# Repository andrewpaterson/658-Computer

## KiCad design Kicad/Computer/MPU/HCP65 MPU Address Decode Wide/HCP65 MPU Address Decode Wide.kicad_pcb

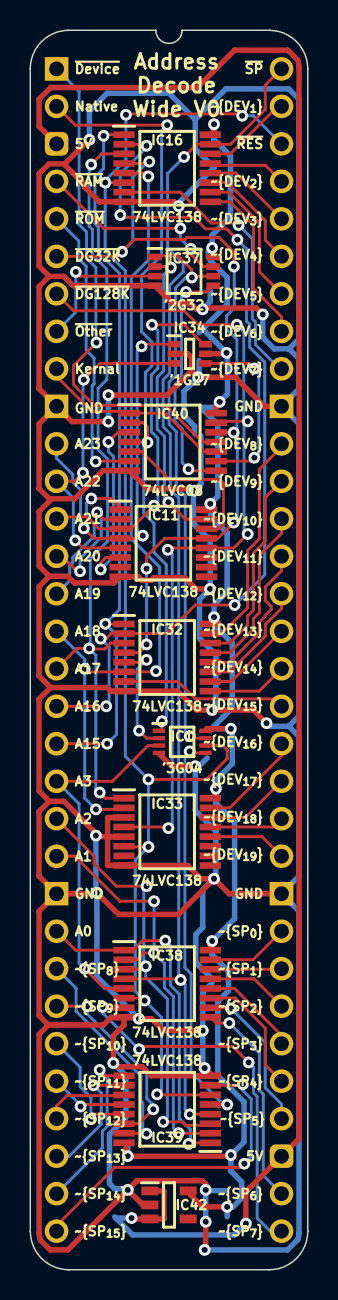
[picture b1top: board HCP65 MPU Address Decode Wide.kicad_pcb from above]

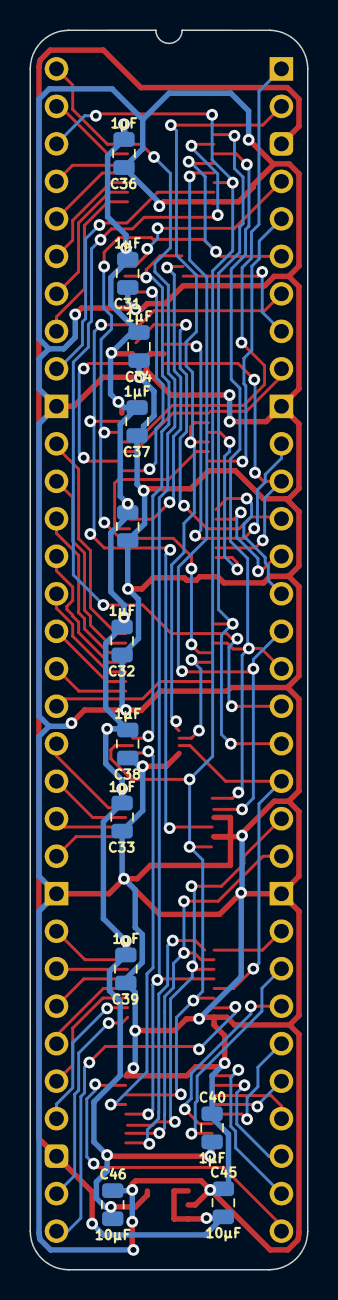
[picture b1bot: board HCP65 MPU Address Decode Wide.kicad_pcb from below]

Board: 2 copper layers, 18.8 x 84.0 mm, 26 parts (14 on the bottom side), 69 nets.

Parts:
C31, C32, C33, C34, C35, C36, C37, C38, C39, C40: 1μF; C_0805
C45, C46: 10μF; C_0805
IC1: SN74LVC3G04DCUR; SOP50P310X90-8N
IC11, IC16, IC32, IC33, IC38, IC39: 74LVC138APW-Q100J; SOP65P640X110-16N
IC34: 74LVC1G27GW,125; SOP65P210X110-6N
IC37: 74LVC2G32DP,125; SOP65P400X110-8N
IC40: 74LVC08APW,112; SOP65P640X110-14N
IC42: AP7365-33WG-7; SOT95P285X130-5N
J1, J3: Pin_Header_01x32; PinHeader_1x32_P2.54mm_Vertical
J2: Conn_02x32_Counter_Clockwise; DIP-64_Board_W15.24mm

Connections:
5V: C45.1, IC42.1 (6VIn), IC42.3 (EN), J2.3, J2.35
/3.3V: C31.1, C32.1, C33.1, C34.1, C35.1, C36.1, C37.1, C38.1, C39.1, C40.1, C46.1, IC1.8 (3V), IC11.16 (3V), IC16.16 (3V), IC32.16 (3V), IC33.16 (3V), IC34.5 (3V), IC37.8 (VCC), IC38.16 (3V), IC39.16 (3V), IC40.14 (3V), IC42.5 (3.3VOut)
/Kernal Mode·Native Latch: IC11.6 (E3), IC40.3 (1Y)
/Reset: IC1.2 (3Y), IC32.5 (~E2)
/~A3: IC1.5 (2Y), IC39.5 (~E2)
/~A21+A22+A23: IC34.4 (Y), IC40.9 (3A)
/~Native Latch: IC1.7 (1Y), IC37.1 (1A), IC37.6 (2B)
/~RAM: IC11.15 (~Y0), IC37.2 (1B)
/~ROM: IC11.14 (~Y1), IC40.5 (2B)
A0: IC38.1 (A0), IC39.1 (A0), J2.24
A1: IC38.2 (A1), IC39.2 (A1), J2.22
A2: IC38.3 (A2), IC39.3 (A2), J2.21
A3: IC1.3 (2A), IC38.5 (~E2), J2.20
A15: IC16.1 (A0), IC32.1 (A0), J2.19
A16: IC16.2 (A1), IC32.2 (A1), J2.18
A17: IC16.3 (A2), IC32.3 (A2), IC33.1 (A0), J2.17
A18: IC16.5 (~E2), IC32.6 (E3), IC33.2 (A1), J2.16
A19: IC11.1 (A0), J2.15
A20: IC11.2 (A1), J2.14
A21: IC11.3 (A2), IC34.6 (C), J2.13
A22: IC11.5 (~E2), IC34.3 (B), J2.12
A23: IC11.4 (~E1), IC34.1 (A), J2.11
GND: C31.2, C32.2, C33.2, C34.2, C35.2, C36.2, C37.2, C38.2, C39.2, C40.2, C45.2, C46.2, IC1.4 (GND), IC11.8 (GND), IC16.8 (GND), IC32.8 (GND), IC33.3 (A2), IC33.5 (~E2), IC33.8 (GND), IC34.2 (GND), IC37.4 (GND), IC38.8 (GND), IC39.8 (GND), IC40.7 (GND), IC42.2 (GND), J2.10, J2.23, J2.42, J2.55
Kernal Mode: IC40.1 (1A), IC40.10 (3B), J2.9
Native Latch: IC1.1 (1A), IC40.2 (1B), IC40.4 (2A), J2.2
unnamed: IC37.5 (2A), IC40.8 (3Y)
~Device Group 32K: IC11.13 (~Y2), IC16.4 (~E1), IC32.4 (~E1), IC40.12 (4A), J2.6
~Device Group 128K: IC11.12 (~Y3), IC33.4 (~E1), IC40.13 (4B), J2.7
~Device _{CS1}: IC16.14 (~Y1), J2.63
~Device _{CS2}: IC16.13 (~Y2), J2.61
~Device _{CS3}: IC16.12 (~Y3), J2.60
~Device _{CS4}: IC16.11 (~Y4), J2.59
~Device _{CS5}: IC16.10 (~Y5), J2.58
~Device _{CS6}: IC16.9 (~Y6), J2.57
~Device _{CS7}: IC16.7 (~Y7), J2.56
~Device _{CS8}: IC32.15 (~Y0), J2.54
~Device _{CS9}: IC32.14 (~Y1), J2.53
~Device _{CS10}: IC32.13 (~Y2), J2.52
~Device _{CS11}: IC32.12 (~Y3), J2.51
~Device _{CS12}: IC32.11 (~Y4), J2.50
~Device _{CS13}: IC32.10 (~Y5), J2.49
~Device _{CS14}: IC32.9 (~Y6), J2.48
~Device _{CS15}: IC32.7 (~Y7), J2.47
~Device _{CS16}: IC33.15 (~Y0), J2.46
~Device _{CS17}: IC33.14 (~Y1), J2.45
~Device _{CS18}: IC33.13 (~Y2), J2.44
~Device _{CS19}: IC33.12 (~Y3), J2.43
~Device: IC40.11 (4Y), J2.1
~OTHER: IC37.3 (2Y), J2.8
~RAM_{CS}: IC37.7 (1Y), J2.4
~ROM_{CS}: IC40.6 (2Y), J2.5
~Reset: IC1.6 (3A), IC16.6 (E3), IC33.6 (E3), IC38.6 (E3), IC39.6 (E3), J2.62
~SPECIAL: IC16.15 (~Y0), IC38.4 (~E1), IC39.4 (~E1), J2.64
~Special _{CS0}: IC38.15 (~Y0), J2.41
~Special _{CS1}: IC38.14 (~Y1), J2.40
~Special _{CS2}: IC38.13 (~Y2), J2.39
~Special _{CS3}: IC38.12 (~Y3), J2.38
~Special _{CS4}: IC38.11 (~Y4), J2.37
~Special _{CS5}: IC38.10 (~Y5), J2.36
~Special _{CS6}: IC38.9 (~Y6), J2.34
~Special _{CS7}: IC38.7 (~Y7), J2.33
~Special _{CS8}: IC39.15 (~Y0), J2.25
~Special _{CS9}: IC39.14 (~Y1), J2.26
~Special _{CS10}: IC39.13 (~Y2), J2.27
~Special _{CS11}: IC39.12 (~Y3), J2.28
~Special _{CS12}: IC39.11 (~Y4), J2.29
~Special _{CS13}: IC39.10 (~Y5), J2.30
~Special _{CS14}: IC39.9 (~Y6), J2.31
~Special _{CS15}: IC39.7 (~Y7), J2.32

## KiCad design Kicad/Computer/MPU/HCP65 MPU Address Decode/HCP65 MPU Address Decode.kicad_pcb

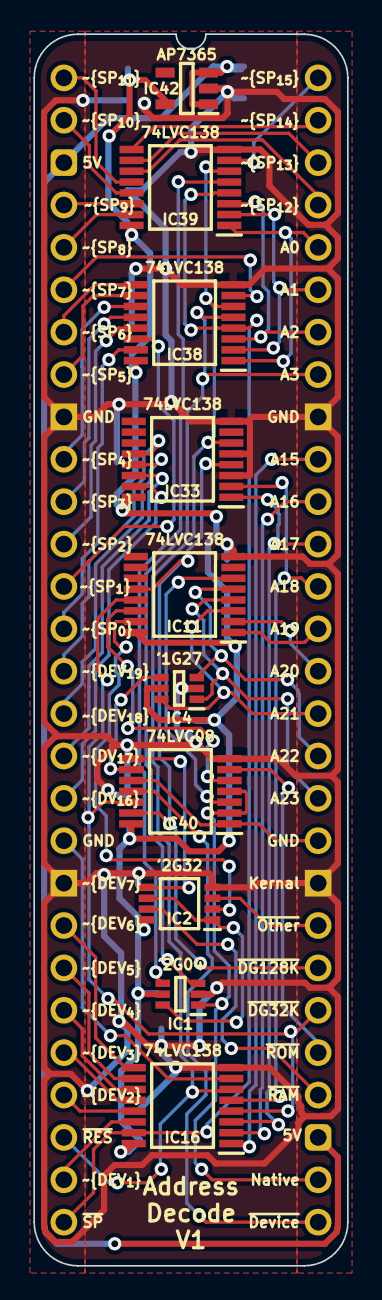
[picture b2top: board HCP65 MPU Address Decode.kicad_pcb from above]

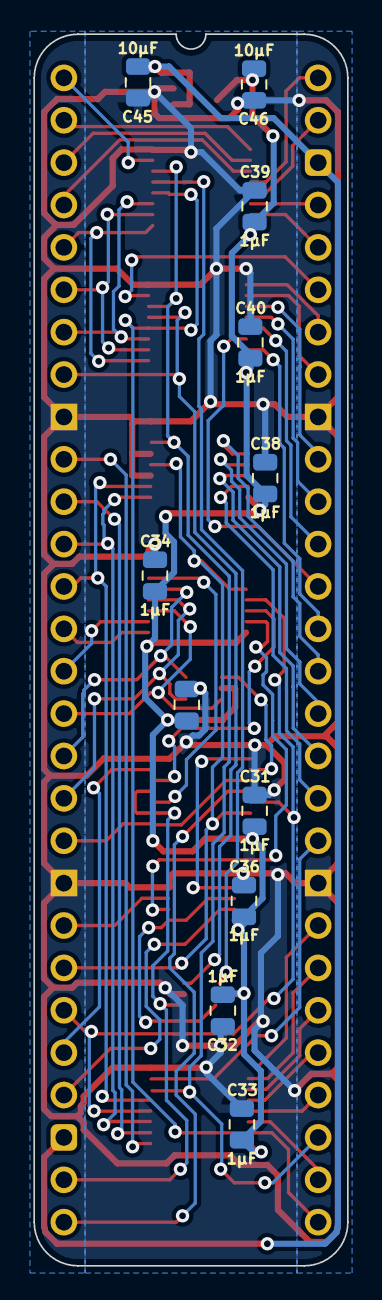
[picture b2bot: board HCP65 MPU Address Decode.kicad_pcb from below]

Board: 2 copper layers, 18.8 x 73.8 mm, 24 parts (13 on the bottom side), 60 nets.

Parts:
C31, C32, C33, C34, C35, C36, C38, C39, C40: 1μF; C_0805
C45, C46: 10μF; C_0805
IC1: 74LVC2G04GW-Q100H; SOP65P210X110-6N
IC2: 74LVC2G32DP,125; SOP65P400X110-8N
IC4: 74LVC1G27GW,125; SOP65P210X110-6N
IC11, IC16, IC33, IC38, IC39: 74LVC138APW-Q100J; SOP65P640X110-16N
IC40: 74LVC08APW,112; SOP65P640X110-14N
IC42: AP7365-33WG-7; SOT95P285X130-5N
J1, J3: Pin_Header_01x28; PinHeader_1x28_P2.54mm_Vertical
J2: Conn_02x28_Counter_Clockwise; DIP-56_Board_W15.24mm

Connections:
5V: C45.1, IC42.1 (6VIn), IC42.3 (EN), J2.3, J2.31
/3.3V: C31.1, C32.1, C33.1, C34.1, C35.1, C36.1, C38.1, C39.1, C40.1, C46.1, IC1.5 (3V), IC2.8 (VCC), IC4.5 (3V), IC11.16 (3V), IC16.16 (3V), IC33.16 (3V), IC38.16 (3V), IC39.16 (3V), IC40.14 (3V), IC42.5 (3.3VOut)
/Kernal Mode·Native Latch: IC11.6 (E3), IC40.3 (1Y)
/~A3: IC1.4 (2Y), IC39.5 (~E2)
/~A21+A22+A23: IC4.4 (Y), IC40.9 (3A)
/~Native Latch: IC1.6 (1Y), IC2.1 (1A), IC2.6 (2B)
/~RAM: IC2.2 (1B), IC11.15 (~Y0)
/~ROM: IC11.14 (~Y1), IC40.5 (2B)
A0: IC38.1 (A0), IC39.1 (A0), J2.52
A1: IC38.2 (A1), IC39.2 (A1), J2.51
A2: IC38.3 (A2), IC39.3 (A2), J2.50
A3: IC1.3 (2A), IC38.5 (~E2), J2.49
A15: IC16.1 (A0), J2.47
A16: IC16.2 (A1), J2.46
A17: IC16.3 (A2), IC33.1 (A0), J2.45
A18: IC16.5 (~E2), IC33.2 (A1), J2.44
A19: IC11.1 (A0), J2.43
A20: IC11.2 (A1), J2.42
A21: IC4.6 (C), IC11.3 (A2), J2.41
A22: IC4.3 (B), IC11.5 (~E2), J2.40
A23: IC4.1 (A), IC11.4 (~E1), J2.39
GND: C31.2, C32.2, C33.2, C34.2, C35.2, C36.2, C38.2, C39.2, C40.2, C45.2, C46.2, IC1.2 (GND), IC2.4 (GND), IC4.2 (GND), IC11.8 (GND), IC16.8 (GND), IC33.3 (A2), IC33.5 (~E2), IC33.8 (GND), IC38.8 (GND), IC39.8 (GND), IC40.7 (GND), IC42.2 (GND), J2.9, J2.20, J2.37, J2.48
Kernal Mode: IC40.1 (1A), IC40.10 (3B), J2.38
Native Latch: IC1.1 (1A), IC40.2 (1B), IC40.4 (2A), J2.30
unnamed: IC2.5 (2A), IC40.8 (3Y)
~Device Group 32K: IC11.13 (~Y2), IC16.4 (~E1), IC40.12 (4A), J2.34
~Device Group 128K: IC11.12 (~Y3), IC33.4 (~E1), IC40.13 (4B), J2.35
~Device _{CS1}: IC16.14 (~Y1), J2.27
~Device _{CS2}: IC16.13 (~Y2), J2.25
~Device _{CS3}: IC16.12 (~Y3), J2.24
~Device _{CS4}: IC16.11 (~Y4), J2.23
~Device _{CS5}: IC16.10 (~Y5), J2.22
~Device _{CS6}: IC16.9 (~Y6), J2.21
~Device _{CS7}: IC16.7 (~Y7), J2.19
~Device _{CS16}: IC33.15 (~Y0), J2.18
~Device _{CS17}: IC33.14 (~Y1), J2.17
~Device _{CS18}: IC33.13 (~Y2), J2.16
~Device _{CS19}: IC33.12 (~Y3), J2.15
~Device: IC40.11 (4Y), J2.29
~OTHER: IC2.3 (2Y), J2.36
~RAM_{CS}: IC2.7 (1Y), J2.32
~ROM_{CS}: IC40.6 (2Y), J2.33
~Reset: IC16.6 (E3), IC33.6 (E3), IC38.6 (E3), IC39.6 (E3), J2.26
~SPECIAL: IC16.15 (~Y0), IC38.4 (~E1), IC39.4 (~E1), J2.28
~Special _{CS0}: IC38.15 (~Y0), J2.14
~Special _{CS1}: IC38.14 (~Y1), J2.13
~Special _{CS2}: IC38.13 (~Y2), J2.12
~Special _{CS3}: IC38.12 (~Y3), J2.11
~Special _{CS4}: IC38.11 (~Y4), J2.10
~Special _{CS5}: IC38.10 (~Y5), J2.8
~Special _{CS6}: IC38.9 (~Y6), J2.7
~Special _{CS7}: IC38.7 (~Y7), J2.6
~Special _{CS8}: IC39.15 (~Y0), J2.5
~Special _{CS9}: IC39.14 (~Y1), J2.4
~Special _{CS10}: IC39.13 (~Y2), J2.2
~Special _{CS11}: IC39.12 (~Y3), J2.1
~Special _{CS12}: IC39.11 (~Y4), J2.53
~Special _{CS13}: IC39.10 (~Y5), J2.54
~Special _{CS14}: IC39.9 (~Y6), J2.55
~Special _{CS15}: IC39.7 (~Y7), J2.56

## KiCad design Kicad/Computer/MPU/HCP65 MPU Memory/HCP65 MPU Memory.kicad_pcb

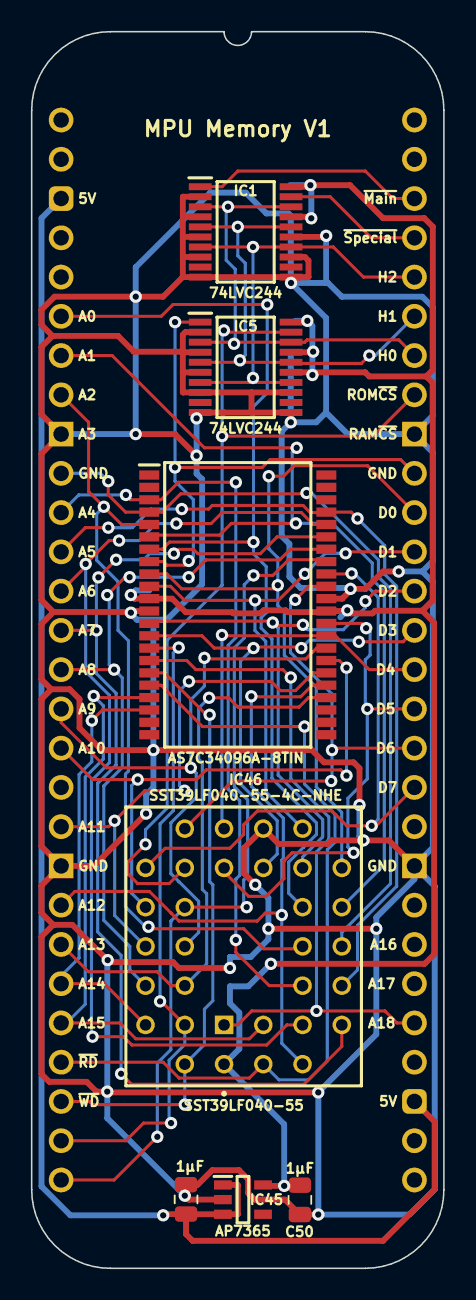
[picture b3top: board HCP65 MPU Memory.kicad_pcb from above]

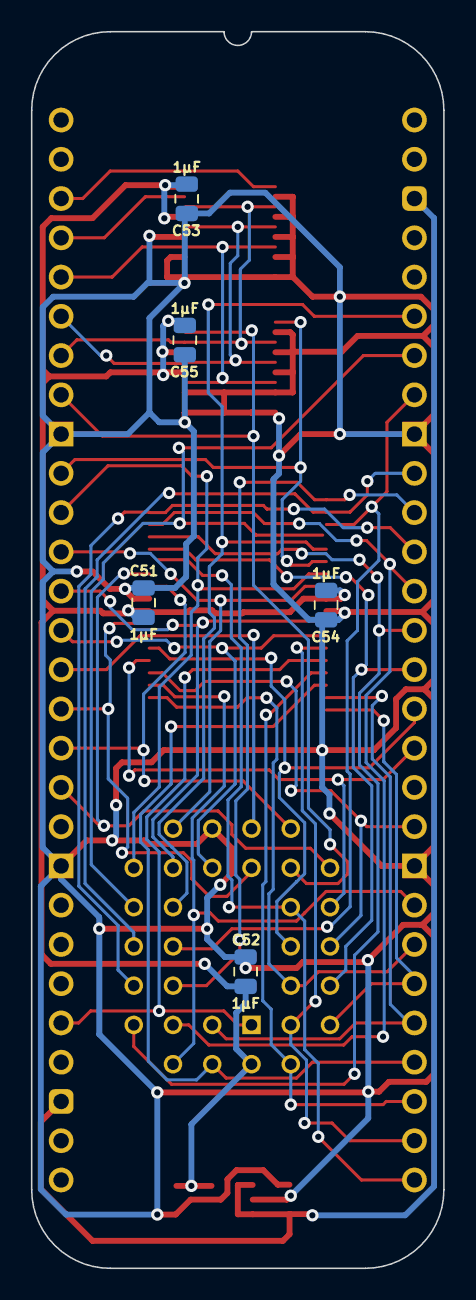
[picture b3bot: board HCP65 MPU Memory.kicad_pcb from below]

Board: 2 copper layers, 26.7 x 80.0 mm, 15 parts (7 on the bottom side), 39 nets.

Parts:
C49, C50, C51, C52, C53, C54, C55: 1μF; C_0805
IC1, IC5: 74LVC244APW,118; SOP65P640X110-20N
IC25: AS7C34096A-8TIN; SOP80P1176X120-44N
IC45: AP7365-33WG-7; SOT95P285X130-5N
IC46: SST39LF040-55-4C-NHE; 5408803224008
J1, J2: Pin_Header_01x20; PinHeader_1x28_P2.54mm_Vertical
J8: Conn_02x28_Counter_Clockwise; DIP-56_Board_W22.86mm

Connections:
5V: C49.1, IC45.1 (6VIn), IC45.3 (EN), J8.3, J8.31
/3.3V: C50.1, C51.1, C52.1, C53.1, C54.1, C55.1, IC1.17 (2A0), IC1.20 (3V), IC5.15 (2A1), IC5.17 (2A0), IC5.20 (3V), IC25.11 (3V), IC25.33 (3V), IC45.5 (3.3VOut), IC46.32 (3V)
A0: IC25.7 (A0), IC46.12 (A0), J8.6
A1: IC25.6 (A1), IC46.11 (A1), J8.7
A2: IC25.5 (A2), IC46.10 (A2), J8.8
A3: IC25.4 (A3), IC46.9 (A3), J8.10
A4: IC25.3 (A4), IC46.8 (A4), J8.11
A5: IC25.41 (A5), IC46.7 (A5), J8.12
A6: IC25.40 (A6), IC46.6 (A6), J8.13
A7: IC25.39 (A7), IC46.5 (A7), J8.14
A8: IC25.38 (A8), IC46.27 (A8), J8.15
A9: IC25.30 (A9), IC46.26 (A9), J8.16
A10: IC25.29 (A10), IC46.23 (A10), J8.17
A11: IC25.28 (A11), IC46.25 (A11), J8.19
A12: IC25.27 (A12), IC46.4 (A12), J8.21
A13: IC25.26 (A13), IC46.28 (A13), J8.22
A14: IC25.20 (A14), IC46.29 (A14), J8.23
A15: IC25.19 (A15), IC46.3 (A15), J8.24
A16: IC25.18 (A16), IC46.2 (A16), J8.25
A17: IC25.17 (A17), IC46.30 (A17), J8.26
A18: IC25.16 (A18), IC46.1 (A18), J8.33
CH0_{OUT}: IC1.3 (2Y0), IC1.18 (1Y0), IC5.3 (2Y0), IC5.18 (1Y0), J8.50
CH1_{OUT}: IC1.5 (2Y1), IC1.16 (1Y1), IC5.5 (2Y1), IC5.16 (1Y1), J8.51
CH2_{OUT}: IC1.7 (2Y2), IC1.14 (1Y2), IC5.7 (2Y2), IC5.14 (1Y2), J8.52
D0: IC25.9 (D0), IC46.13 (DQ0), J8.46
D1: IC25.10 (D1), IC46.14 (DQ1), J8.45
D2: IC25.13 (D2), IC46.15 (DQ2), J8.44
D3: IC25.14 (D3), IC46.17 (DQ3), J8.43
D4: IC25.31 (D4), IC46.18 (DQ4), J8.42
D5: IC25.32 (D5), IC46.19 (DQ5), J8.41
D6: IC25.35 (D6), IC46.20 (DQ6), J8.40
D7: IC25.36 (D7), IC46.21 (DQ7), J8.39
GND: C49.2, C50.2, C51.2, C52.2, C53.2, C54.2, C55.2, IC1.2 (1A0), IC1.4 (1A1), IC1.6 (1A2), IC1.8 (1A3), IC1.10 (GND), IC1.11 (2A3), IC1.13 (2A2), IC1.15 (2A1), IC5.2 (1A0), IC5.4 (1A1), IC5.6 (1A2), IC5.8 (1A3), IC5.10 (GND), IC5.11 (2A3), IC5.13 (2A2), IC25.12 (GND), IC25.34 (GND), IC45.2 (GND), IC46.16 (GND), J8.9, J8.20, J8.37, J8.48
~Main: IC1.1 (~1OE), J8.54
~RAM_{CS}: IC5.1 (~1OE), IC25.8 (~CE), J8.47
~RD: IC25.37 (~OE), IC46.24 (~OE), J8.28
~ROM_{CS}: IC5.19 (~2OE), IC46.22 (~CE), J8.49
~Special: IC1.19 (~2OE), J8.53
~WD: IC25.15 (~WE), IC46.31 (~WE), J8.27

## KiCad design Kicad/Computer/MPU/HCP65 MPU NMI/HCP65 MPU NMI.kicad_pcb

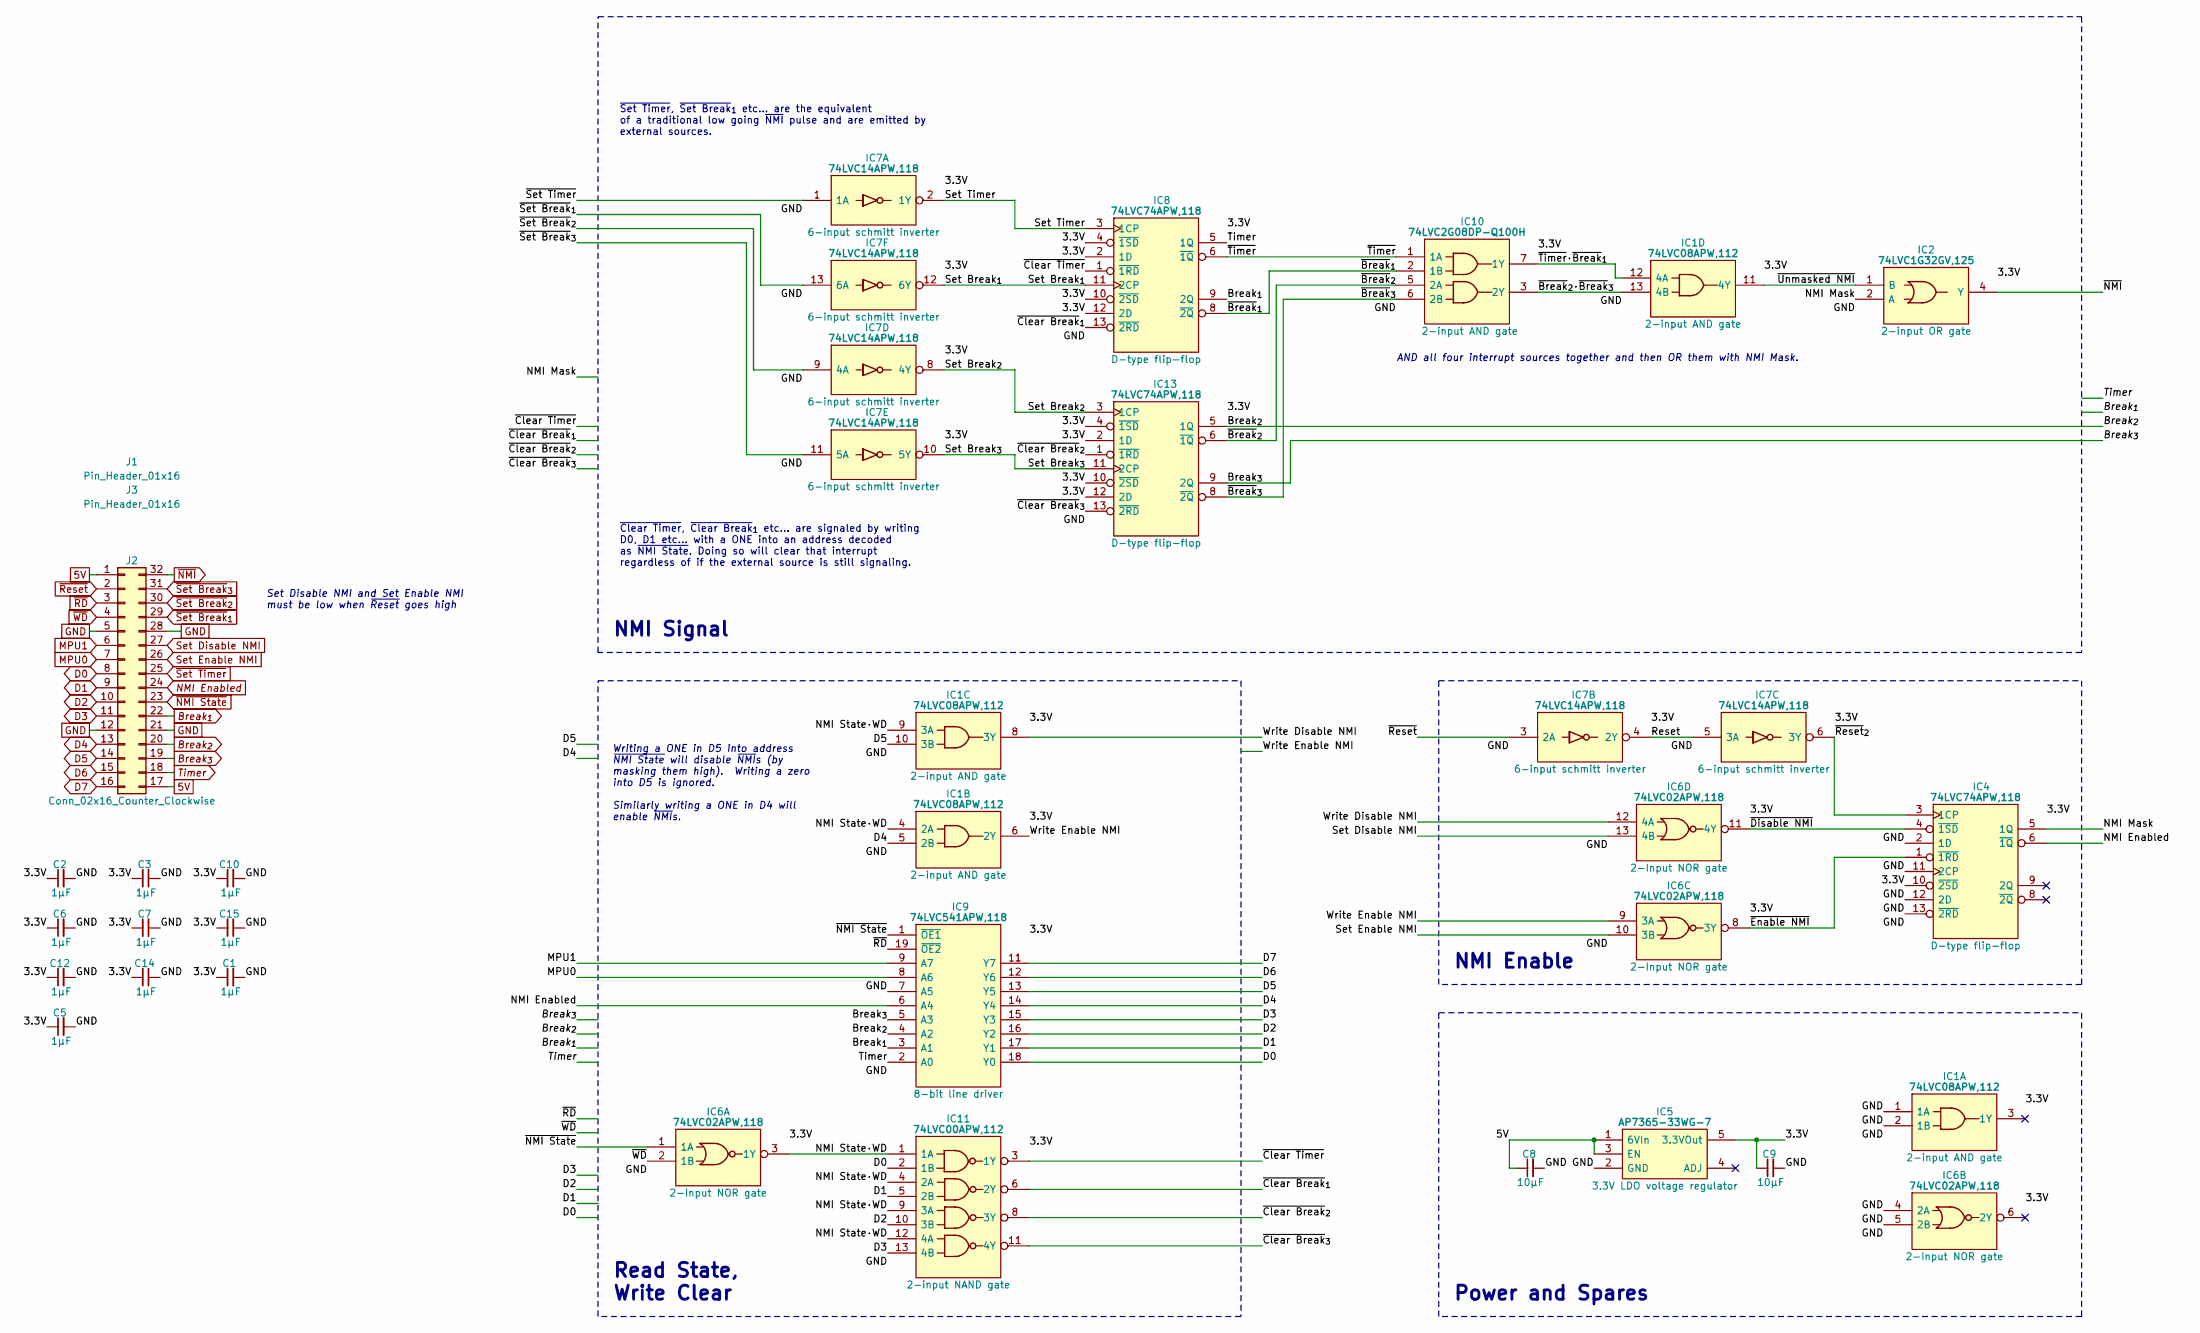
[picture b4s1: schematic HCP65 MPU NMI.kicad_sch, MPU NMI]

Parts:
C1, C2, C3, C5, C6, C7, C10, C12, C14, C15: 1μF; C_0805
C8, C9: 10µF; C_0805
IC1: 74LVC08APW,112; SOP65P640X110-14N; Manufacturer_Part_Number 74LVC08APW,112; Mouser Part Number 771-74LVC08APW
IC2: 74LVC1G32GV,125; SOT95P275X110-5N; Manufacturer_Part_Number 74LVC1G32GV,125; Mouser Part Number 771-LVC1G32GV125
IC4, IC8, IC13: 74LVC74APW,118; SOP65P640X110-14N; Mouser Part Number 771-74LVC74APW-T
IC5: AP7365-33WG-7; SOT95P285X130-5N; Manufacturer_Part_Number AP7365-33WG-7; Mouser Part Number 621-AP7365-33WG-7
IC6: 74LVC02APW,118; SOP65P640X110-14N; Mouser Part Number 771-74LVC02APW-T
IC7: 74LVC14APW,118; SOP65P640X110-14N; Manufacturer_Part_Number 74LVC14APW,118; Mouser Part Number 771-74LVC14APW-T
IC9: 74LVC541APW,118; SOP65P640X110-20N; Mouser Part Number 771-74LVC541APW-T
IC10: 74LVC2G08DP-Q100H; SOP65P400X110-8N; Manufacturer_Part_Number 74LVC2G08DP-Q100H; Mouser Part Number 771-74LVC2G08DPQ100H
IC11: 74LVC00APW,112; SOP65P640X110-14N; Mouser Part Number 771-74LVC00APW
J1, J3: Pin_Header_01x16; PinHeader_1x16_P2.54mm_Vertical
J2: Conn_02x16_Counter_Clockwise; DIP-32_Board_W22.86mm

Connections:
5V: C8.1, IC5.1 (6VIn), IC5.3 (EN), J2.1, J2.17
/3.3V: C1.1, C2.1, C3.1, C5.1, C6.1, C7.1, C9.1, C10.1, C12.1, C14.1, C15.1, IC1.14 (3V), IC2.5 (3V), IC4.10 (~2SD), IC4.14 (3V), IC5.5 (3.3VOut), IC6.14 (3V), IC7.14 (3V), IC8.2 (1D), IC8.4 (~1SD), IC8.10 (~2SD), IC8.12 (2D), IC8.14 (3V), IC9.20 (3V), IC10.8 (3V), IC11.14 (3V), IC13.2 (1D), IC13.4 (~1SD), IC13.10 (~2SD), IC13.12 (2D), IC13.14 (3V)
/NMI Mask: IC2.2 (A), IC4.5 (1Q)
/NMI State·WD: IC1.4 (2A), IC1.9 (3A), IC6.3 (1Y), IC11.1 (1A), IC11.4 (2A), IC11.9 (3A), IC11.12 (4A)
/Reset: IC7.4 (2Y), IC7.5 (3A)
/Set Break_{1}: IC7.12 (6Y), IC8.11 (2CP)
/Set Break_{2}: IC7.8 (4Y), IC13.3 (1CP)
/Set Break_{3}: IC7.10 (5Y), IC13.11 (2CP)
/Set Timer: IC7.2 (1Y), IC8.3 (1CP)
/Write Disable NMI: IC1.8 (3Y), IC6.12 (4A)
/Write Enable NMI: IC1.6 (2Y), IC6.9 (3A)
/~Break_{1}: IC8.8 (~2Q), IC10.2 (1B)
/~Break_{2}: IC10.5 (2A), IC13.6 (~1Q)
/~Break_{2}·~Break_{3}: IC1.13 (4B), IC10.3 (2Y)
/~Break_{3}: IC10.6 (2B), IC13.8 (~2Q)
/~Clear Break_{1}: IC8.13 (~2RD), IC11.6 (2Y)
/~Clear Break_{2}: IC11.8 (3Y), IC13.1 (~1RD)
/~Clear Break_{3}: IC11.11 (4Y), IC13.13 (~2RD)
/~Clear Timer: IC8.1 (~1RD), IC11.3 (1Y)
/~Disable NMI: IC4.4 (~1SD), IC6.11 (4Y)
/~Enable NMI: IC4.1 (~1RD), IC6.8 (3Y)
/~Reset_{2}: IC4.3 (1CP), IC7.6 (3Y)
/~Timer: IC8.6 (~1Q), IC10.1 (1A)
/~Timer·~Break_{1}: IC1.12 (4A), IC10.7 (1Y)
/~Unmasked NMI: IC1.11 (4Y), IC2.1 (B)
Break_{1}: IC8.9 (2Q), IC9.3 (A1), J2.22
Break_{2}: IC9.4 (A2), IC13.5 (1Q), J2.20
Break_{3}: IC9.5 (A3), IC13.9 (2Q), J2.19
D0: IC9.18 (Y0), IC11.2 (1B), J2.8
D1: IC9.17 (Y1), IC11.5 (2B), J2.9
D2: IC9.16 (Y2), IC11.10 (3B), J2.10
D3: IC9.15 (Y3), IC11.13 (4B), J2.11
D4: IC1.5 (2B), IC9.14 (Y4), J2.13
D5: IC1.10 (3B), IC9.13 (Y5), J2.14
D6: IC9.12 (Y6), J2.15
D7: IC9.11 (Y7), J2.16
GND: C1.2, C2.2, C3.2, C5.2, C6.2, C7.2, C8.2, C9.2, C10.2, C12.2, C14.2, C15.2, IC1.1 (1A), IC1.2 (1B), IC1.7 (GND), IC2.3 (GND), IC4.2 (1D), IC4.7 (GND), IC4.11 (2CP), IC4.12 (2D), IC4.13 (~2RD), IC5.2 (GND), IC6.4 (2A), IC6.5 (2B), IC6.7 (GND), IC7.7 (GND), IC8.7 (GND), IC9.7 (A5), IC9.10 (GND), IC10.4 (GND), IC11.7 (GND), IC13.7 (GND), J2.5, J2.12, J2.21, J2.28
MPU0: IC9.8 (A6), J2.7
MPU1: IC9.9 (A7), J2.6
NMI Enabled: IC4.6 (~1Q), IC9.6 (A4), J2.24
Set Disable NMI: IC6.13 (4B), J2.27
Set Enable NMI: IC6.10 (3B), J2.26
Timer: IC8.5 (1Q), IC9.2 (A0), J2.18
~NMI State: IC6.1 (1A), IC9.1 (~OE1), J2.23
~NMI: IC2.4 (Y), J2.32
~RD: IC9.19 (~OE2), J2.3
~Reset: IC7.3 (2A), J2.2
~Set Break_{1}: IC7.13 (6A), J2.29
~Set Break_{2}: IC7.9 (4A), J2.30
~Set Break_{3}: IC7.11 (5A), J2.31
~Set Timer: IC7.1 (1A), J2.25
~WD: IC6.2 (1B), J2.4

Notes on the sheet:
AND all four interrupt sources together and then OR them with NMI Mask.
NMI Enable
Set Disable NMI and Set Enable NMI must be low when ~{Reset} goes high
Read State, Write Clear
Writing a ONE in D5 into address ~{NMI State} will disable ~{NMI}s (by masking them high). Writing a zero into D5 is ignored. Similarly writing a ONE in D4 will enable ~{NMI}s.
NMI Signal
Power and Spares
~{Set Timer}, ~{Set Break}_{1} etc... are the equivalent of a traditional low going ~{NMI} pulse and are emitted by external sources.
~{Clear Timer}, ~{Clear Break}_{1} etc... are signaled by writing D0, D1 etc... with a ONE into an address decoded as ~{NMI State}. Doing so will clear that interrupt regardless of if the external source is still signaling.

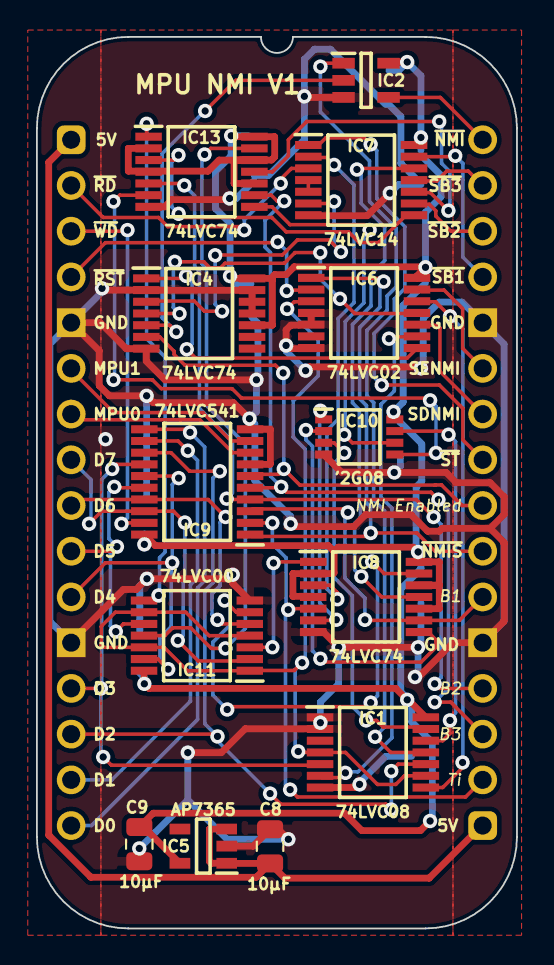
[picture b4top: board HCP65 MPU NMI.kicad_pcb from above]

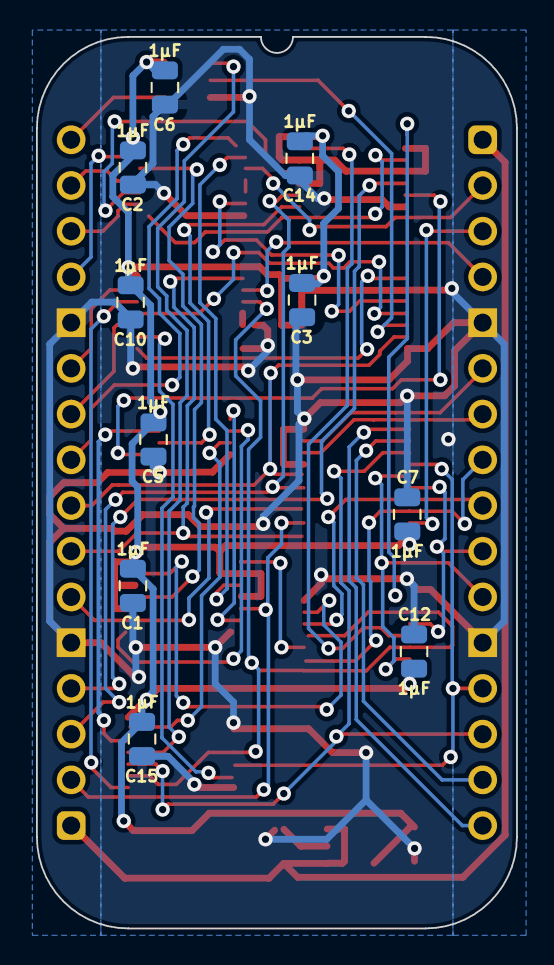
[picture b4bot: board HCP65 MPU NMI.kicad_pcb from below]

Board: 2 copper layers, 26.7 x 49.5 mm, 26 parts (12 on the bottom side), 52 nets.

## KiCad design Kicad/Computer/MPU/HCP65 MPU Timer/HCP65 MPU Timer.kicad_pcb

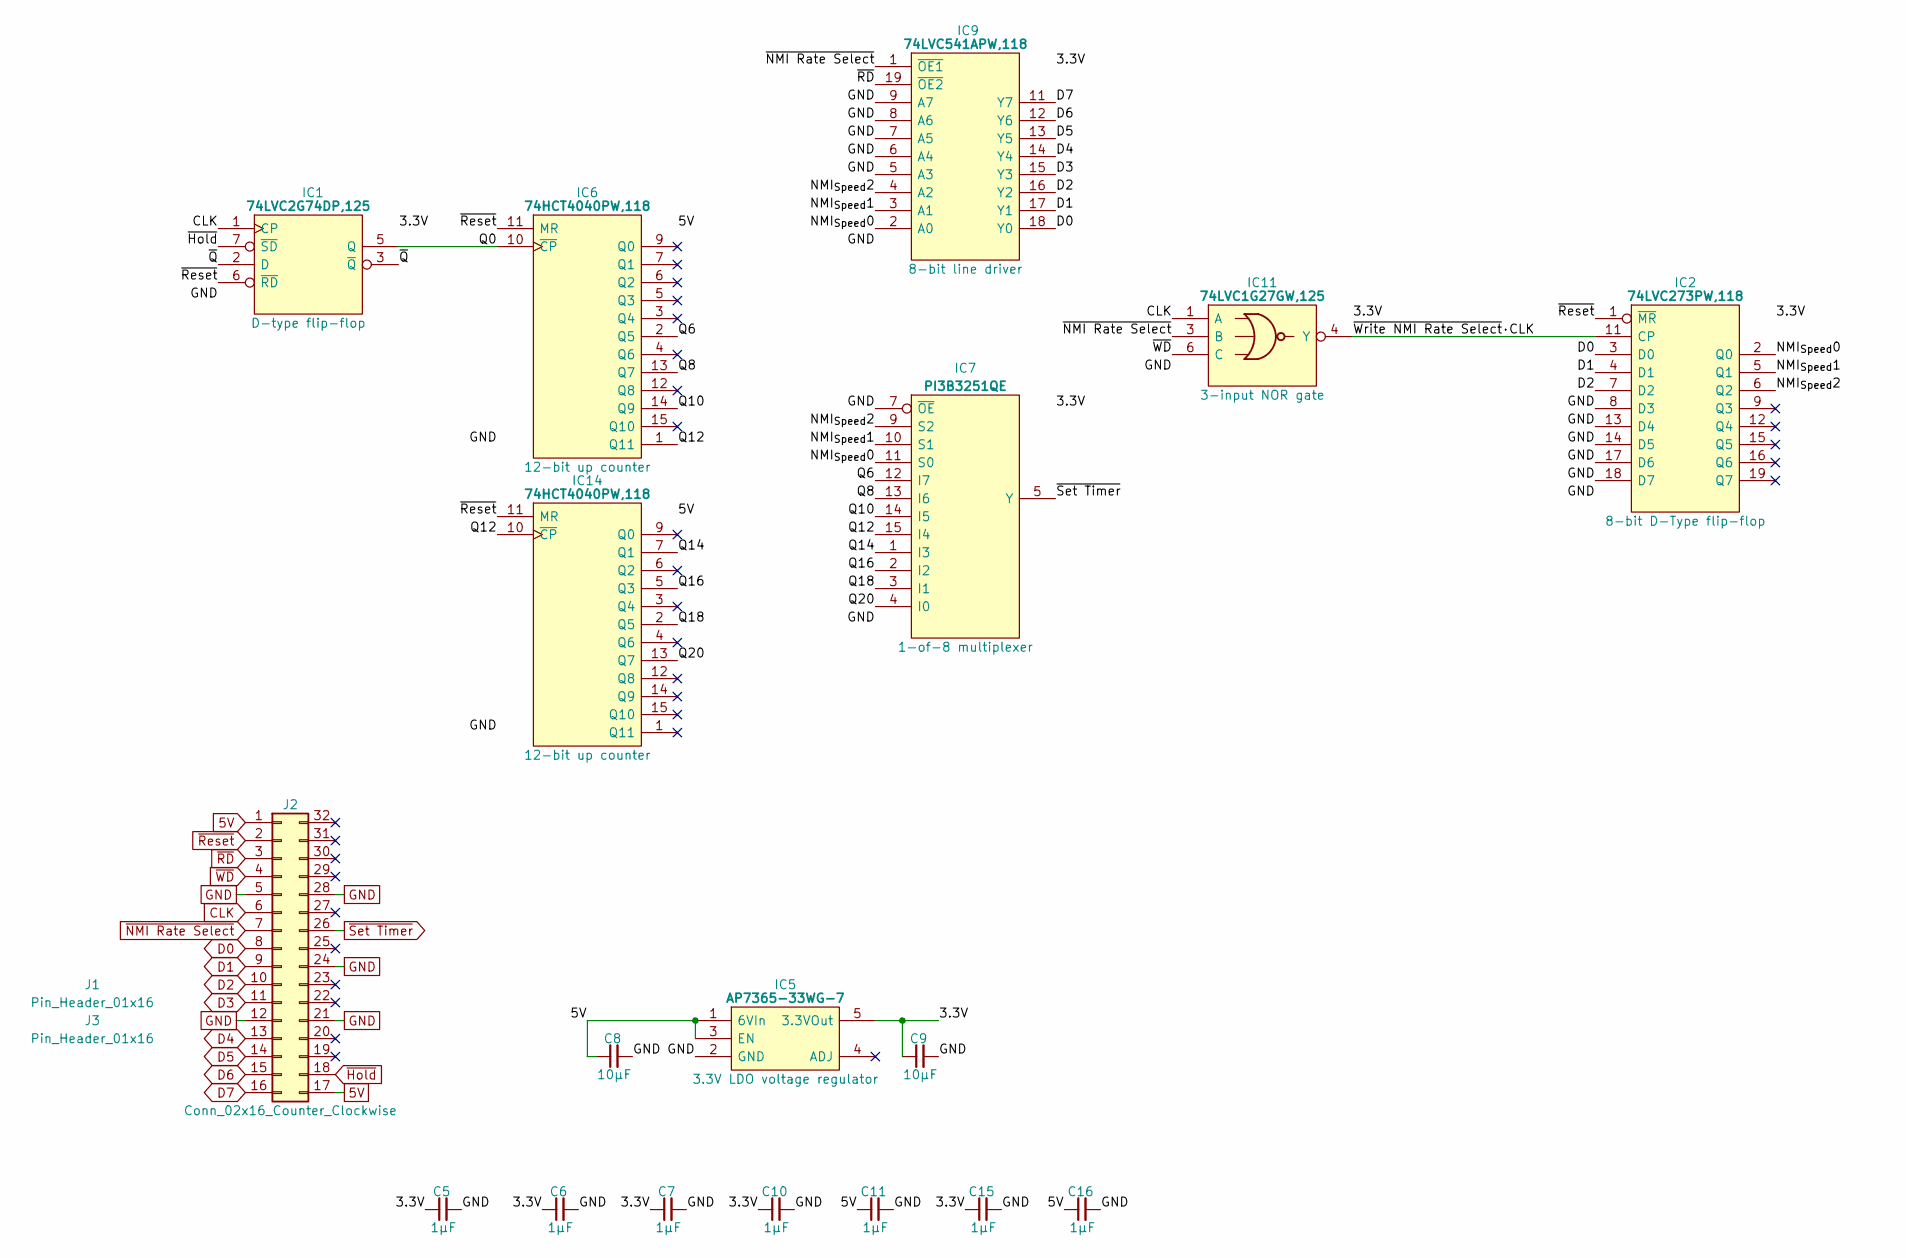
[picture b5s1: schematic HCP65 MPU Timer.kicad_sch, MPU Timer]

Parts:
C5, C6, C7, C10, C11, C15, C16: 1μF; C_0805
C8, C9: 10µF; C_0805
IC1: 74LVC2G74DP,125; SOP65P400X110-8N; Manufacturer_Part_Number 74LVC2G74DP,125; Mouser Part Number 771-74LVC2G74DP-G
IC2: 74LVC273PW,118; SOP65P640X110-20N; Manufacturer_Part_Number 74LVC273PW,118; Mouser Part Number 771-74LVC273PW-T
IC5: AP7365-33WG-7; SOT95P285X130-5N; Manufacturer_Part_Number AP7365-33WG-7; Mouser Part Number 621-AP7365-33WG-7
IC6, IC14: 74HCT4040PW,118; SOP65P640X110-16N; Manufacturer_Part_Number 74HCT4040PW,118; Mouser Part Number 771-HCT4040PW118
IC7: PI3B3251QE; SOP64P599X175-16N; Manufacturer_Part_Number PI3B3251QE; Mouser Part Number 729-PI3B3251QE
IC9: 74LVC541APW,118; SOP65P640X110-20N; Mouser Part Number 771-74LVC541APW-T
IC11: 74LVC1G27GW,125; SOP65P210X110-6N; Mouser Part Number 771-74LVC1G27GW125
J1, J3: Pin_Header_01x16; PinHeader_1x16_P2.54mm_Vertical
J2: Conn_02x16_Counter_Clockwise; DIP-32_Board_W15.24mm

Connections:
5V: C8.1, C11.1, C16.1, IC5.1 (6VIn), IC5.3 (EN), IC6.16 (5V), IC14.16 (5V), J2.1, J2.17
/3.3V: C5.1, C6.1, C7.1, C9.1, C10.1, C15.1, IC1.8 (3V), IC2.20 (3V), IC5.5 (3.3VOut), IC7.16 (3V), IC9.20 (3V), IC11.5 (3V)
/NMI_{Speed}0: IC2.2 (Q0), IC7.11 (S0), IC9.2 (A0)
/NMI_{Speed}1: IC2.5 (Q1), IC7.10 (S1), IC9.3 (A1)
/NMI_{Speed}2: IC2.6 (Q2), IC7.9 (S2), IC9.4 (A2)
/Q0: IC1.5 (Q), IC6.10 (~CP)
/Q6: IC6.2 (Q5), IC7.12 (I7)
/Q8: IC6.13 (Q7), IC7.13 (I6)
/Q10: IC6.14 (Q9), IC7.14 (I5)
/Q12: IC6.1 (Q11), IC7.15 (I4), IC14.10 (~CP)
/Q14: IC7.1 (I3), IC14.7 (Q1)
/Q16: IC7.2 (I2), IC14.5 (Q3)
/Q18: IC7.3 (I1), IC14.2 (Q5)
/Q20: IC7.4 (I0), IC14.13 (Q7)
/~Q: IC1.2 (D), IC1.3 (~Q)
/~Write NMI Rate Select·CLK: IC2.11 (CP), IC11.4 (Y)
CLK: IC1.1 (CP), IC11.1 (A), J2.6
D0: IC2.3 (D0), IC9.18 (Y0), J2.8
D1: IC2.4 (D1), IC9.17 (Y1), J2.9
D2: IC2.7 (D2), IC9.16 (Y2), J2.10
D3: IC9.15 (Y3), J2.11
D4: IC9.14 (Y4), J2.13
D5: IC9.13 (Y5), J2.14
D6: IC9.12 (Y6), J2.15
D7: IC9.11 (Y7), J2.16
GND: C5.2, C6.2, C7.2, C8.2, C9.2, C10.2, C11.2, C15.2, C16.2, IC1.4 (GND), IC2.8 (D3), IC2.10 (GND), IC2.13 (D4), IC2.14 (D5), IC2.17 (D6), IC2.18 (D7), IC5.2 (GND), IC6.8 (GND), IC7.7 (~OE), IC7.8 (GND), IC9.5 (A3), IC9.6 (A4), IC9.7 (A5), IC9.8 (A6), IC9.9 (A7), IC9.10 (GND), IC11.2 (GND), IC14.8 (GND), J2.5, J2.12, J2.21, J2.24, J2.28
~Hold: IC1.7 (~SD), J2.18
~NMI Rate Select: IC9.1 (~OE1), IC11.3 (B), J2.7
~RD: IC9.19 (~OE2), J2.3
~Reset: IC1.6 (~RD), IC2.1 (~MR), IC6.11 (MR), IC14.11 (MR), J2.2
~Set Timer: IC7.5 (Y), J2.26
~WD: IC11.6 (C), J2.4

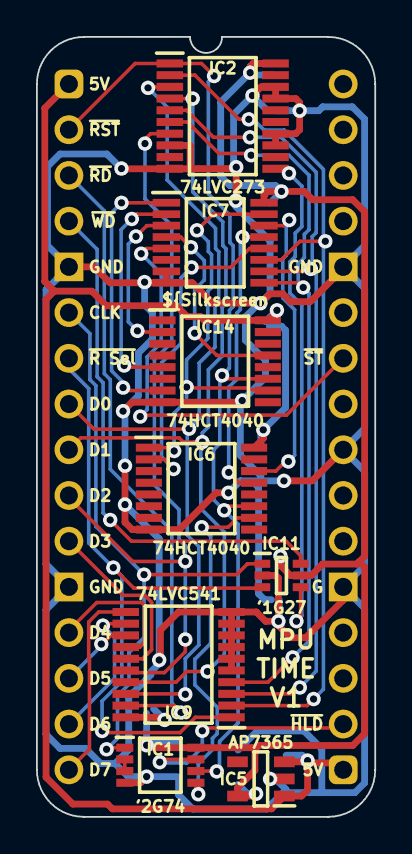
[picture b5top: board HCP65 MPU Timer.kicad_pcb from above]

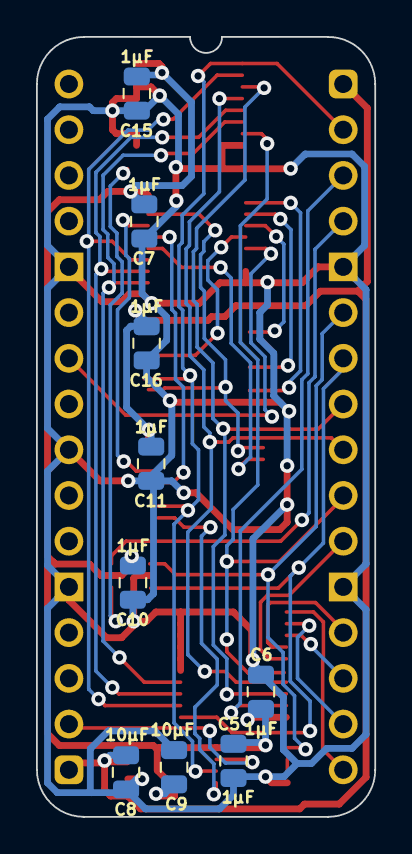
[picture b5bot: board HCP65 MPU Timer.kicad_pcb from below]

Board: 2 copper layers, 18.8 x 43.3 mm, 20 parts (11 on the bottom side), 32 nets.
